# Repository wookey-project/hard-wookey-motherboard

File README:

# WooKey Mainboard PCB

## Introduction

Wookey | https://wookey-project.github.io/
Copyright 2018 The wookey project team <wookey@ssi.gouv.fr>

The Wookey from [ANSSI](https://www.ssi.gouv.fr) is an open source
hardware design, implementing an Encrypted Flash Drives.

This repository is aimed towards developers.

### Revision information

This directory contains the hardware design for the Wookey board, first public version (Wookey V2).

### PCB editing tools

All PCB files (schematic and PCB layout) have been designed using the KiCad EDA.
This Cross Platform and Open Source Electronics Design Automation Suite can be downloaded
on http://kicad-pcb.org/.

## Production files generation 101

### Configure the project

KiCad binaries location may change regarding your operating system.
This is why you have to set your environment.
This is done by sourcing the `setenv.sh` script. This script exports
all paths that are required in order to automaticaly generate the production files.

Most of the time, the paths proposed in this script are not the one you use in your specific installation.
The `setenv.sh` script support easy variables overloading by including a `setenv.local.sh` script file if this file exists in the same directory.
If you need to overload some of the variables of the `setenv.sh` script, just add them to your own `setenv.local.sh` file.
Here is an example to define KiCad environement path on Apple Mac OS.

```
  $ echo "export PYTHON_BIN_PATH = /Applications/KiCad/kicad.app/Contents/Frameworks/Python.framework/Versions/2.7/bin/python" > setenv.local.sh
  $ source setenv.sh
  Loading local SDK settings...
  =========================================================
  === Kicad environment configuration
  =========================================================
  PYTHON_BIN_PATH   = /Applications/KiCad/kicad.app/Contents/Frameworks/Python.framework/Versions/2.7/bin/python
  PYTHON_PATH     = /Applications/Kicad/kicad.app/Contents/Frameworks/python/site-packages
  BOM_GEN_PATH = /Applications/Kicad/kicad.app/Contents/SharedSupport/plugins/bom2grouped_csv.xsl
  TOOLS_PATH = ../../../tools
  =========================================================
```

The production files can be generated using the following command.

```
$ make
```

This will generate the production files in a new sub directory.
The directory name may differ according the project your are working with.

## PCB Pinout

## PCB Layers

### PCB TOP layer

### PCB BOTTOM layer

### Layers

Order and type of copper layers:
  TOP:  signal, front components
  GND:  ground plane
  PWR:  ground and power plane
  BOT:  signal, back components

### Stackup
4 layers, 1.6mm thickness
Outer layers 1 oz base copper foil
Inner layers 0.5 oz base copper foil

Electroless Nickel Immersion Gold (ENIG) surface finish

solder resist   0.0254mm
copper          0.0356mm    L1 (TOP)
FR408 prepreg   0.1702mm
copper          0.0178mm    L2 (GND)
FR408           1.1938mm
copper          0.0178mm    L3 (PWR)
FR408 prepreg   0.1702mm
copper          0.0356mm    L4 (BOT)
solder resist   0.0254mm

The substrate for both the core and prepreg is FR408,
with a dielectric constant of 3.66 at 1GHz.
The prepreg is comprised of 2 layers of Isola 2113.

## Regulatory compliance & handling

The Wookey board is intended for use as a development platform for hardware
or software. The board is an open system design, which does not include a
shielded enclosure. This may cause interference to other electrical or
electronic devices in close proximity. In a domestic environment, this product
may cause radio interference in which case the user may be required to take
adequate measures. In addition, this board should not be used near any medical
equipment or RF devices.

The board is sensitive to ESD. Hold the board only by its edges. After removing
the board from its box, place it on a grounded, static-free surface.

The board can become hot, like any fan-less design, during continuous high CPU
loads, mind its temperature while handling it.

## License

Wookey | https://wookey-project.github.io/
Copyright 2018 The wookey project team <wookey@ssi.gouv.fr>

This is an open hardware design licensed under the terms of the CERN Open
Hardware Licence (OHL) v1.2.

You may redistribute and modify this documentation under the terms of the CERN
OHL v.1.2 (http://ohwr.org/cernohl). This documentation is distributed WITHOUT
ANY EXPRESS OR IMPLIED WARRANTY, INCLUDING OF MERCHANTABILITY, SATISFACTORY
QUALITY AND FITNESS FOR A PARTICULAR PURPOSE. Please see the CERN OHL v.1.2 for
applicable conditions.

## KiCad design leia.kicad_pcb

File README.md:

# WooKey Mainboard PCB

## Introduction

Wookey | https://wookey-project.github.io/
Copyright 2018 ANSSI

Authors: The Wookey project Team <wookey@ssi.gouv.fr>

The Wookey from [ANSSI](https://www.ssi.gouv.fr) is an open source
hardware design, implementing an Encrypted Flash Drives.

This repository is aimed towards developers.

### Revision information

This directory contains the hardware design for the Wookey board, first public version (Wookey V2).

### PCB editing tools

All PCB files (schematic and PCB layout) have been designed using the KiCad EDA.
This Cross Platform and Open Source Electronics Design Automation Suite can be downloaded
on http://kicad.org/.

## Production files generation 101

### Configure the project

KiCad binaries location may change regarding your operating system.
This is why you have to set your environment.
This is done by sourcing the `setenv.sh` script. This script exports
all paths that are required in order to automaticaly generate the production files.

Most of the time, the paths proposed in this script are not the one you use in your specific installation.
The `setenv.sh` script support easy variables overloading by including a `setenv.local.sh` script file if this file exists in the same directory.
If you need to overload some of the variables of the `setenv.sh` script, just add them to your own `setenv.local.sh` file.
Here is an example to define KiCad environement path on Apple Mac OS.

```
  $ echo "export PYTHON_BIN_PATH = /Applications/KiCad/kicad.app/Contents/Frameworks/Python.framework/Versions/2.7/bin/python" > setenv.local.sh
  $ source setenv.sh
  Loading local SDK settings...
  =========================================================
  === Kicad environment configuration
  =========================================================
  PYTHON_BIN_PATH   = /Applications/KiCad/kicad.app/Contents/Frameworks/Python.framework/Versions/2.7/bin/python
  PYTHON_PATH     = /Applications/Kicad/kicad.app/Contents/Frameworks/python/site-packages
  BOM_GEN_PATH = /Applications/Kicad/kicad.app/Contents/SharedSupport/plugins/bom2grouped_csv.xsl
  TOOLS_PATH = ../../../tools
  =========================================================
```

The production files can be generated using the following command.

```
$ make
```

This will generate the production files in a new sub directory.
The directory name may differ according the project your are working with.

## PCB Pinout

## PCB Layers

### PCB TOP layer

### PCB BOTTOM layer

### Layers

Order and type of copper layers:
  TOP:  signal, front components
  GND:  ground plane
  PWR:  ground and power plane
  BOT:  signal, back components

### Stackup
4 layers, 1.6mm thickness
Outer layers 1 oz base copper foil
Inner layers 0.5 oz base copper foil

Electroless Nickel Immersion Gold (ENIG) surface finish

solder resist   0.0254mm
copper          0.0356mm    L1 (TOP)
FR408 prepreg   0.1702mm
copper          0.0178mm    L2 (GND)
FR408           1.1938mm
copper          0.0178mm    L3 (PWR)
FR408 prepreg   0.1702mm
copper          0.0356mm    L4 (BOT)
solder resist   0.0254mm

The substrate for both the core and prepreg is FR408,
with a dielectric constant of 3.66 at 1GHz.
The prepreg is comprised of 2 layers of Isola 2113.

## Regulatory compliance & handling

The Wookey board is intended for use as a development platform for hardware
or software. The board is an open system design, which does not include a
shielded enclosure. This may cause interference to other electrical or
electronic devices in close proximity. In a domestic environment, this product
may cause radio interference in which case the user may be required to take
adequate measures. In addition, this board should not be used near any medical
equipment or RF devices.

The board is sensitive to ESD. Hold the board only by its edges. After removing
the board from its box, place it on a grounded, static-free surface.

The board can become hot, like any fan-less design, during continuous high CPU
loads, mind its temperature while handling it.

## License

Wookey | https://wookey-project.github.io/

Copyright 2019 ANSSI

Authors: The Wookey project Team <wookey@ssi.gouv.fr>

This is an open hardware design licensed under the terms of the CERN Open
Hardware Licence (OHL) v1.2.

You may redistribute and modify this documentation under the terms of the CERN
OHL v.1.2 (http://ohwr.org/cernohl). This documentation is distributed WITHOUT
ANY EXPRESS OR IMPLIED WARRANTY, INCLUDING OF MERCHANTABILITY, SATISFACTORY
QUALITY AND FITNESS FOR A PARTICULAR PURPOSE. Please see the CERN OHL v.1.2 for
applicable conditions.

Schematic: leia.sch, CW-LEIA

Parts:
C1003, C4004: 0.1uF 35V Tant; CP_EIA-3216-18_Kemet-A; MFG Part Num T491A104K035AT
FID1001, FID1002, FID1003, FID1004, FID1005, FID1006: FIDUCIAL-RESCUE-rescue; Fiducial_1mm_Mask2mm
HOLE1, HOLE2: HOLE; MountingHole_2.2mm_M2_ISO14580_Pad
J6: EXT_READER_VCC; SMA_Amphenol_132289_EdgeMount; MFG Part Num 132289
J1002: READER_GND; PinHeader_2x03_P2.54mm_Vertical; MFG Part Num 90131-0763
J1003: READER_VDD; PinHeader_2x03_P2.54mm_Vertical; MFG Part Num 90131-0763
J1101: TARGET_PWR; PinHeader_2x03_P2.54mm_Vertical; MFG Part Num 90131-0763
J1102: TARGET_GND; PinHeader_2x03_P2.54mm_Vertical; MFG Part Num 90131-0763
J1103: TARGET_EXT_PWR; SMA_Amphenol_132289_EdgeMount; MFG Part Num 132289
J1112: TARGET_SHUNT; SMA_Amphenol_132289_EdgeMount; MFG Part Num 132289
JP1102: SHUNT Bypass; PinHeader_1x02_P2.54mm_Vertical; MFG Part Num 90120-0762
P523: CMD; PinHeader_2x04_P2.54mm_Vertical; MFG Part Num 826632-4
R1112: 0.1 1%; R_0603_1608Metric; MFG Part Num RL0603FR-070R1L
TP1001: VDDD; TestPoint_Keystone_5000-5004_Miniature; MFG Part Num 5003
TP1002: DGND; TestPoint_Keystone_5000-5004_Miniature; MFG Part Num 5002; Mouser Price/Stock 2301279
TP1101: VDDA; TestPoint_Pad_D1.0mm
TP1112: GNDA; TestPoint_Pad_D1.0mm
TP5001: VDDA; TestPoint_Keystone_5000-5004_Miniature; MFG Part Num 5000
TP5002: GNDA; TestPoint_Keystone_5000-5004_Miniature; MFG Part Num 5001; Mouser Price/Stock 5001
U520: FOD8012A; SOIC-8_3.9x4.9mm_P1.27mm

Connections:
/EXT_READER_GND: J6.2 (Ext), J1002.6
/EXT_READER_VCC: J6.1 (In), J1003.5
/GNDCARD: J1112.1 (In), JP1102.1, R1112.1; also elsewhere on the board
/GND_CONSOLE: C1003.2, P523.7, U520.5 (GND2)
/RX_CMD: U520.2 (VOA); also elsewhere on the board
/RX_CONSOLE: P523.3, U520.7 (VINA)
/TX_CMD: U520.3 (VINB); also elsewhere on the board
/TX_CONSOLE: P523.5, U520.6 (VOB)
/USB_READER_VCC: J1003.1; also elsewhere on the board
/VDD_CONSOLE: C1003.1, P523.1, U520.8 (VDD2)
/iface_ufo/RX: P523.6; also elsewhere on the board
/iface_ufo/TX: P523.4; also elsewhere on the board
GND: J1102.2; also elsewhere on the board
GNDA: J1102.1, J1102.3, J1102.5, J1112.2 (Ext), JP1102.2, P523.8, R1112.2, TP1112.1, TP5002.1; also elsewhere on the board
GNDD: C4004.2, J1002.1, J1002.3, J1002.5, TP1002.1, U520.4 (GND1); also elsewhere on the board
GNDPWR: J1002.2; also elsewhere on the board
unnamed: J1101.6, J1103.1 (In)
unnamed: J1102.6, J1103.2 (Ext)
VCOM: J1101.2; also elsewhere on the board
VDD: C4004.1, J1003.2, J1003.4, J1003.6, TP1001.1, U520.1 (VDD1); also elsewhere on the board
VDDA: J1101.1, J1101.3, J1101.5, P523.2, TP1101.1, TP5001.1; also elsewhere on the board

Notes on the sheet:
Since LEIA embed an SMA for the shunt resistor, we do not need to connect SHUNT signal to the CW308 board
VDDD and GNDD are connected to optocouplers reader side
User can choose between external power supply or CW power supply.
User can choose to connect the CMD Console to the CW or something else. In this case optocoupler power supply should be provided by the device connected to the CMD Console.
JMP 1101 VDDA 1-2 CW-POWER 5-6 EXT-POWER
JMP 1102 GNDA 1-2 CW-GND 5-6 EXT-GND

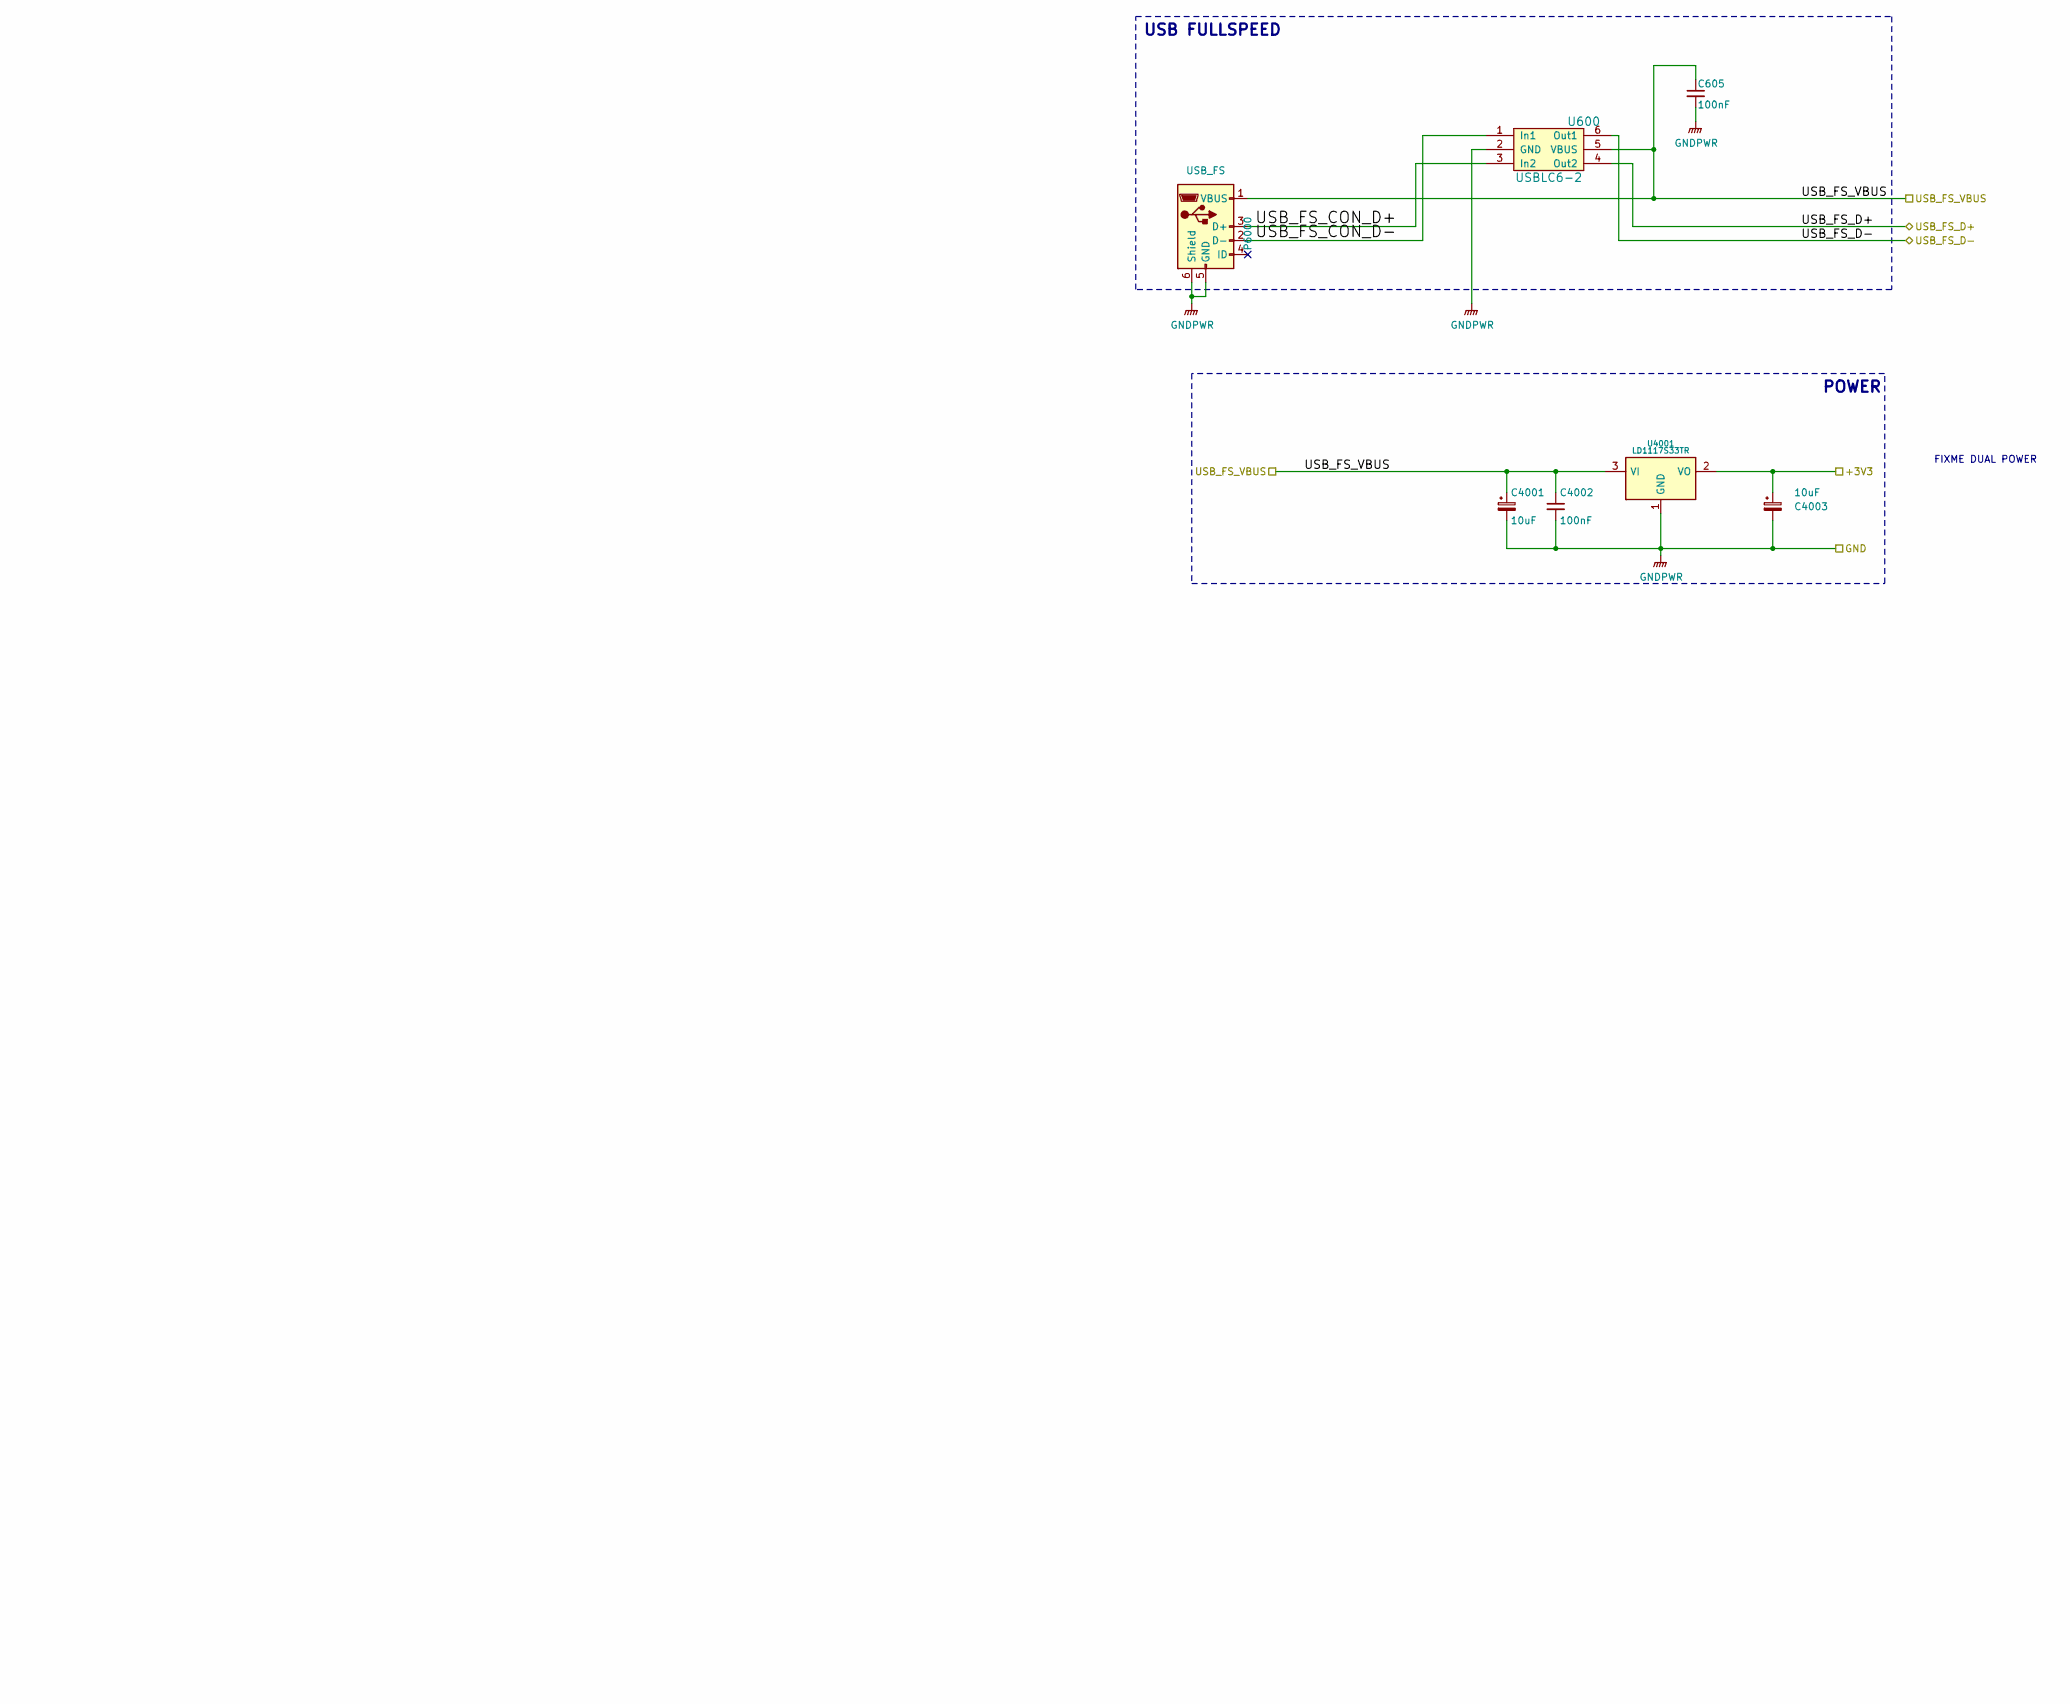
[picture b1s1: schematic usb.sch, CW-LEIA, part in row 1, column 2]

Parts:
C605, C4002: 100nF; C_0603_1608Metric; MFG Part Num GRM188R71H104KA93D
C4001, C4003: 10uF; CP_EIA-3216-18_Kemet-A; MFG Part Num TP8M106M6R3C
P6000: USB_FS; USB_Micro-B-MOLEX_105017-0001; MFG Part Num 105017-0001
U600: USBLC6-2; SOT-23-6; MFG Part Num USBLC6-2SC6
U4001: LD1117S33TR; SOT-223; MFG Part Num LD1117S33TR

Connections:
/USB_READER_VCC: C4003.1, U4001.2 (VO); also elsewhere on the board
/cpu/USB_FS_D+: U600.4 (Out2); also elsewhere on the board
/cpu/USB_FS_D-: U600.6 (Out1); also elsewhere on the board
/cpu/USB_FS_VBUS: C605.1, C4001.1, C4002.1, P6000.1 (VBUS), U600.5 (VBUS), U4001.3 (VI); also elsewhere on the board
/usb/USB_FS_CON_D+: P6000.3 (D+), U600.3 (In2)
/usb/USB_FS_CON_D-: P6000.2 (D-), U600.1 (In1)
GNDPWR: C605.2, C4001.2, C4002.2, C4003.2, P6000.5 (GND), P6000.6 (Shield), U600.2 (GND), U4001.1 (GND); also elsewhere on the board

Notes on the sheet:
USB FULLSPEED
POWER
FIXME DUAL POWER

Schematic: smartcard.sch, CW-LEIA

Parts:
C1001: 10uF; C_0603_1608Metric; MFG Part Num TP8M106M6R3C
C1002: 100nF; C_0603_1608Metric; MFG Part Num GRM188R71H104KA93D
C1101, C1108, C1201, C1208, C1301, C1308, C1401, C1408, C1501, C1508, C1601, C1608, C1701, C1708, C1801, C1806, C1902, C5001, C5002, C5003: 0.1uF 35V Tant; CP_EIA-3216-18_Kemet-A; MFG Part Num T491A104K035AT
D3001: VDDA; LED_0603_1608Metric_Castellated; MFG Part Num TLMS1100-GS08..
J1001: FILTER; PinHeader_2x03_P2.54mm_Vertical; MFG Part Num 90131-0763
J1706: TARGET_TRIG; SMA_Amphenol_132289_EdgeMount; MFG Part Num 132289
JP1500: TEARING; PinHeader_1x02_P2.54mm_Vertical; MFG Part Num 90120-0762
P1000: ISO7816_NO; VJW53666; MFG Part Num 7312P0225A13LF
Q5001, Q5002: BSS84; SOT-23; MFG Part Num BSS84
R1001: 20k; R_0603_1608Metric; MFG Part Num RCA060320K0FKEA
R1007, R1422, R1902: 22k; R_0603_1608Metric; MFG Part Num RCA060320K0FKEA
R1306, R1506: 10k; R_0603_1608Metric; MFG Part Num CRCW060310K0JNEA
R3001: 470; R_0603_1608Metric; MFG Part Num CRCW0603470RFKEA
R5002, R5003: DNP; R_0603_1608Metric; MFG Part Num RCA060347K0FKEA
U1100, U1200, U1300, U1400, U1500, U1600, U1700, U1800, U5001: FOD8001; SOIC-8_3.9x4.9mm_P1.27mm; MFG Part Num FOD8001
U1900, U5002: ADG719-EP; TSOT-23-6; MFG Part Num ADG719BRTZ-REEL7

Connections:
/GNDCARD: P1000.C5 (GND); also elsewhere on the board
/cpu/CARD_CLK: U1200.2 (Vin); also elsewhere on the board
/cpu/CARD_CT: U1600.6 (Vout); also elsewhere on the board
/cpu/CARD_IO: U1900.5 (D); also elsewhere on the board
/cpu/CARD_PWR_EN: U1500.2 (Vin); also elsewhere on the board
/cpu/CARD_RESET: U1100.2 (Vin); also elsewhere on the board
/cpu/CARD_VPP: U1300.2 (Vin); also elsewhere on the board
/cpu/CARD_~R~W: U1900.1 (IN), U5001.2 (Vin); also elsewhere on the board
/cpu/TRIGGER: U1700.2 (Vin); also elsewhere on the board
/dfu smartcard/CRD_CLK: P1000.C3 (CLK), U1200.6 (Vout)
/dfu smartcard/CRD_CT: P1000.SW1, R1001.2, U1600.2 (Vin)
/dfu smartcard/CRD_IO: P1000.C7 (I/O), R1007.2, U5002.5 (D)
/dfu smartcard/CRD_PWR: J1001.1, P1000.C1 (VCC), Q5002.3 (D), R1506.1
/dfu smartcard/CRD_RST: P1000.C2 (RST), U1100.6 (Vout)
/dfu smartcard/CRD_VPP: P1000.C6 (VPP), Q5001.3 (D), R1306.1
/dfu smartcard/IO_IN: R1422.2, U1400.2 (Vin), U1900.6 (S2)
/dfu smartcard/IO_OUT: R1902.2, U1800.6 (Vout), U1900.4 (S1)
/dfu smartcard/TRIGGER_OUT: J1706.1 (In), U1700.6 (Vout)
GNDA: C1001.2, C1002.2, C1108.2, C1208.2, C1308.2, C1408.2, C1508.2, C1608.2, C1708.2, C1801.2, C5002.2, C5003.2, D3001.1 (K), J1001.5, J1706.2 (Ext), P1000.SW2, R1306.2, R1506.2, U1100.5 (GND2), U1200.5 (GND2), U1300.5 (GND2), U1400.5 (GND2), U1500.5 (GND2), U1600.4 (GND1), U1700.5 (GND2), U1800.4 (GND1), U5001.5 (GND2), U5002.3 (GND); also elsewhere on the board
GNDD: C1101.2, C1201.2, C1301.2, C1401.2, C1501.2, C1601.2, C1701.2, C1806.2, C1902.2, C5001.2, U1100.4 (GND1), U1200.4 (GND1), U1300.4 (GND1), U1400.4 (GND1), U1500.4 (GND1), U1600.5 (GND2), U1700.4 (GND1), U1800.5 (GND2), U1900.3 (GND), U5001.4 (GND1); also elsewhere on the board
unnamed: C1001.1, C1002.1, J1001.2, J1001.4, J1001.6
unnamed: D3001.2 (A), R3001.2
unnamed: JP1500.1, U1500.6 (Vout)
unnamed: JP1500.2, Q5002.1 (G)
unnamed: Q5001.1 (G), U1300.6 (Vout)
unnamed: R5002.2, U1400.6 (Vout), U5002.6 (S2)
unnamed: R5003.2, U1800.2 (Vin), U5002.4 (S1)
unnamed: U5001.6 (Vout), U5002.1 (IN)
VDD: C1101.1, C1201.1, C1301.1, C1401.1, C1501.1, C1601.1, C1701.1, C1806.1, C1902.1, C5001.1, R1422.1, R1902.1, U1100.1 (VDD1), U1200.1 (VDD1), U1300.1 (VDD1), U1400.1 (VDD1), U1500.1 (VDD1), U1600.8 (VDD2), U1700.1 (VDD1), U1800.8 (VDD2), U1900.2 (VDD), U5001.1 (VDD1); also elsewhere on the board
VDDA: C1108.1, C1208.1, C1308.1, C1408.1, C1508.1, C1608.1, C1708.1, C1801.1, C5002.1, C5003.1, Q5001.2 (S), Q5002.2 (S), R1001.1, R1007.1, R3001.1, R5002.1, R5003.1, U1100.8 (VDD2), U1200.8 (VDD2), U1300.8 (VDD2), U1400.8 (VDD2), U1500.8 (VDD2), U1600.1 (VDD1), U1700.8 (VDD2), U1800.1 (VDD1), U5001.8 (VDD2), U5002.2 (VDD); also elsewhere on the board

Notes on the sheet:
TruthTable VI Vled VO H OFF H L ON L

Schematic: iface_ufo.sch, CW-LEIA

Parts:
J6000: CW308_TARGETCON; CW308T_CONNBOARD
J6200: CW_PWR; PinHeader_2x06_P2.54mm_Vertical; MFG Part Num 90131-0766

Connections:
/iface_ufo/CW308_1.2: J6000.C11 (VCC1.2), J6200.9
/iface_ufo/CW308_1.8: J6000.C12 (VCC1.8), J6200.7
/iface_ufo/CW308_2.5: J6000.C13 (VCC2.5), J6200.5
/iface_ufo/CW308_3.3: J6000.C14 (VCC3.3), J6200.3
/iface_ufo/CW308_5.0: J6000.C15 (VCC5.0), J6200.1
/iface_ufo/RX: J6000.A8 (GPIO2/RX); also elsewhere on the board
/iface_ufo/TX: J6000.A7 (GPIO1/TX); also elsewhere on the board
GND: J6000.C17 (GND); also elsewhere on the board
VCOM: J6000.C8 (FILTIN), J6200.2, J6200.4, J6200.6, J6200.8, J6200.10, J6200.12; also elsewhere on the board
VDDA: J6000.A20 (VREF); also elsewhere on the board

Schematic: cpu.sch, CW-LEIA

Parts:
C500, C506, C511, C514, C519, C521, C522, C528, C550, C575: 100nF; C_0603_1608Metric; MFG Part Num GRM188R71H104KA93D
C549, C573: 2.2uF; C_0603_1608Metric; MFG Part Num GRM188R61C225KE15D
D110: LED BLUE; LED_0603_1608Metric_Castellated; MFG Part Num VLMB1300-GS08
D111: LED GREEN; LED_0603_1608Metric_Castellated; MFG Part Num VLMTG1300-GS08
D112: VDD; LED_0603_1608Metric_Castellated; MFG Part Num TLMS1100-GS08..
JP100: BOOT1; PinHeader_1x02_P2.54mm_Vertical; MFG Part Num 90120-0762
JP101: BOOT0; PinHeader_1x02_P2.54mm_Vertical; MFG Part Num 90120-0762
P542: TP4; TestPoint_Pad_D1.0mm
P543: TP5; TestPoint_Pad_D1.0mm
P545: TP7; TestPoint_Pad_D1.0mm
P546: TP8; TestPoint_Pad_D1.0mm
P547: TP9; TestPoint_Pad_D1.0mm
P548: TP10; TestPoint_Pad_D1.0mm
P592: UART1; PinHeader_1x03_P2.54mm_Vertical; MFG Part Num 90120-0763
P593: SWD; PinHeader_1x05_P2.54mm_Vertical; MFG Part Num 90120-0765
R100, R503, R514: 10K; R_0603_1608Metric; MFG Part Num CRCW060310K0FKEAHP
R104, R110, R111, R112: 470; R_0603_1608Metric; MFG Part Num CRCW0603470RFKEA
SW503: DFU; KSR_TACTILE_SWITCH; MFG Part Num KSR231G LFS
SW514: RESET; KSR_TACTILE_SWITCH; MFG Part Num KSR231G LFS
U500: STM32F439VIT6; TQFP-100_14x14mm_P0.5mm; MFG Part Num STM32F439VIT6

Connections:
/RX_CMD: U500.24 (PA1); also elsewhere on the board
/TX_CMD: U500.23 (PA0); also elsewhere on the board
/cpu/BOOT0: JP101.1, U500.94 (BOOT0)
/cpu/BOOT1: JP100.2, U500.37 (PB2)
/cpu/CARD_CLK: U500.29 (PA4), U500.90 (PB4); also elsewhere on the board
/cpu/CARD_CT: U500.79 (PC11); also elsewhere on the board
/cpu/CARD_IO: U500.25 (PA2); also elsewhere on the board
/cpu/CARD_PWR_EN: U500.88 (PD7); also elsewhere on the board
/cpu/CARD_RESET: U500.80 (PC12); also elsewhere on the board
/cpu/CARD_VPP: U500.78 (PC10); also elsewhere on the board
/cpu/CARD_~R~W: U500.2 (PE3); also elsewhere on the board
/cpu/DFU: R503.1, SW503.2, U500.30 (PA5)
/cpu/LED0_PC4: R111.1, U500.33 (PC4)
/cpu/LED1_PC5: R110.1, U500.34 (PC5)
/cpu/NRST: C514.1, P593.5, R514.2, SW514.1, U500.14 (NRST)
/cpu/TCK: P593.2, U500.76 (PA14)
/cpu/TMS: P593.4, U500.72 (PA13)
/cpu/TRIGGER: U500.77 (PA15); also elsewhere on the board
/cpu/UART1_RX_PB7: P592.2, U500.93 (PB7)
/cpu/UART1_TX_PB6: P592.1, U500.92 (PB6)
/cpu/USB_FS_D+: U500.71 (PA12); also elsewhere on the board
/cpu/USB_FS_D-: U500.70 (PA11); also elsewhere on the board
/cpu/USB_FS_VBUS: U500.68 (PA9); also elsewhere on the board
GNDD: C500.2, C506.2, C511.2, C514.2, C519.2, C521.2, C522.2, C528.2, C549.2, C550.2, C573.2, C575.2, D110.1 (K), D111.1 (K), D112.1 (K), P592.3, P593.3, R104.2, R503.2, SW514.2, U500.10 (VSS), U500.20 (VSSA), U500.27 (VSS), U500.74 (VSS), U500.99 (VSS); also elsewhere on the board
unnamed: C549.1, U500.49 (VCAP_1)
unnamed: C573.1, U500.73 (VCAP_2)
unnamed: D110.2 (A), R110.2
unnamed: D111.2 (A), R111.2
unnamed: D112.2 (A), R112.2
unnamed: JP100.1, R100.2
unnamed: JP101.2, R104.1
unnamed: P542.1, U500.42 (PE11)
unnamed: P543.1, U500.43 (PE12)
unnamed: P545.1, U500.45 (PE14)
unnamed: P546.1, U500.46 (PE15)
unnamed: P547.1, U500.81 (PD0)
unnamed: P548.1, U500.82 (PD1)
VDD: C500.1, C506.1, C511.1, C519.1, C521.1, C522.1, C528.1, C550.1, C575.1, P593.1, R100.1, R112.1, R514.1, SW503.1, U500.6 (VBAT), U500.11 (VDD), U500.19 (VDD), U500.21 (VREF+), U500.22 (VDDA), U500.28 (VDD), U500.50 (VDD), U500.75 (VDD), U500.100 (VDD); also elsewhere on the board

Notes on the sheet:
BOOT MODE
LED
EXTENSION & DEBUG
Boot0 = 0 => Flash memory aliased at 0x0000000
Since the READER and the Target have separated power domains, the reader JTAG and the Debug UART are not connected to the CW308 board.

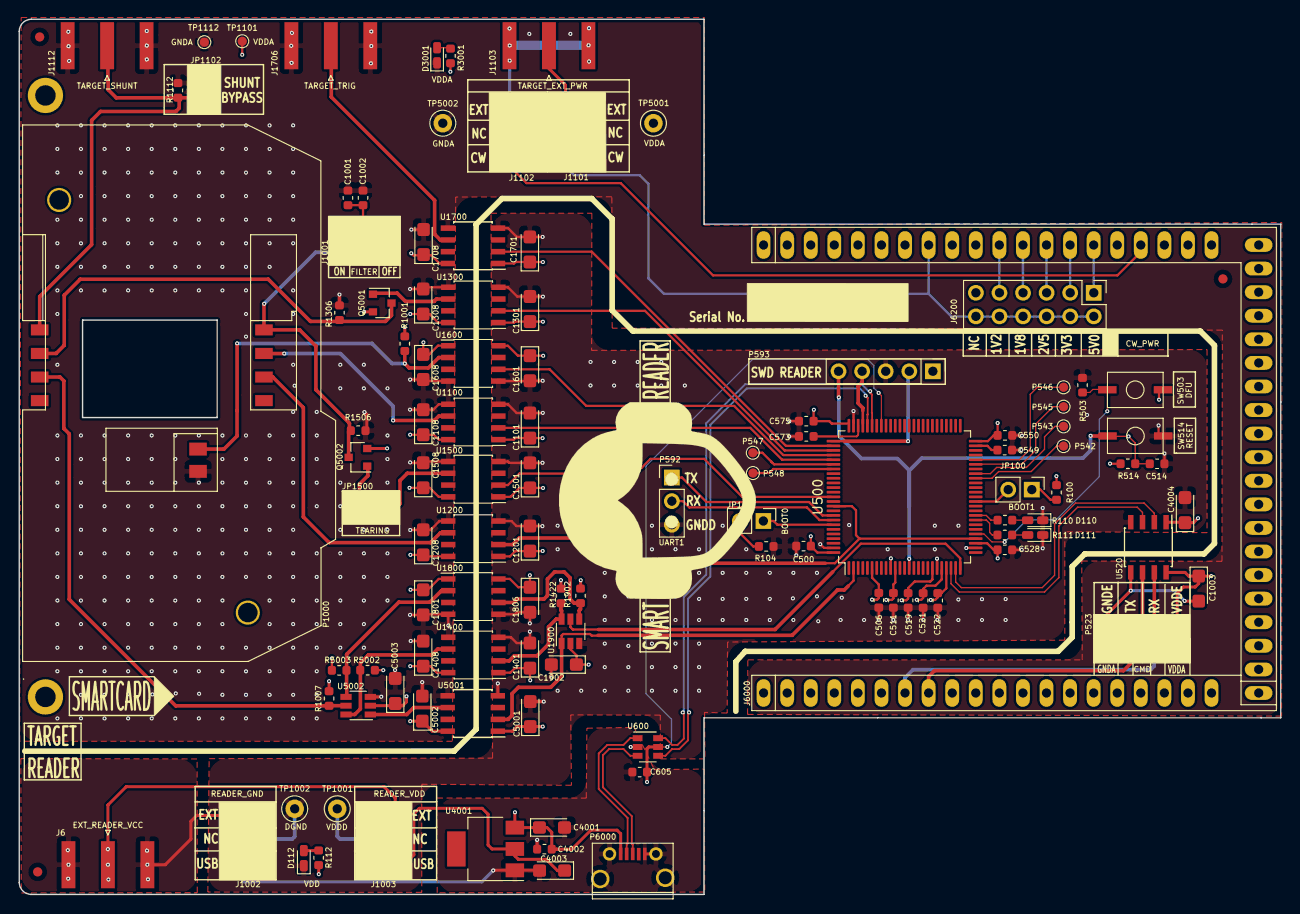
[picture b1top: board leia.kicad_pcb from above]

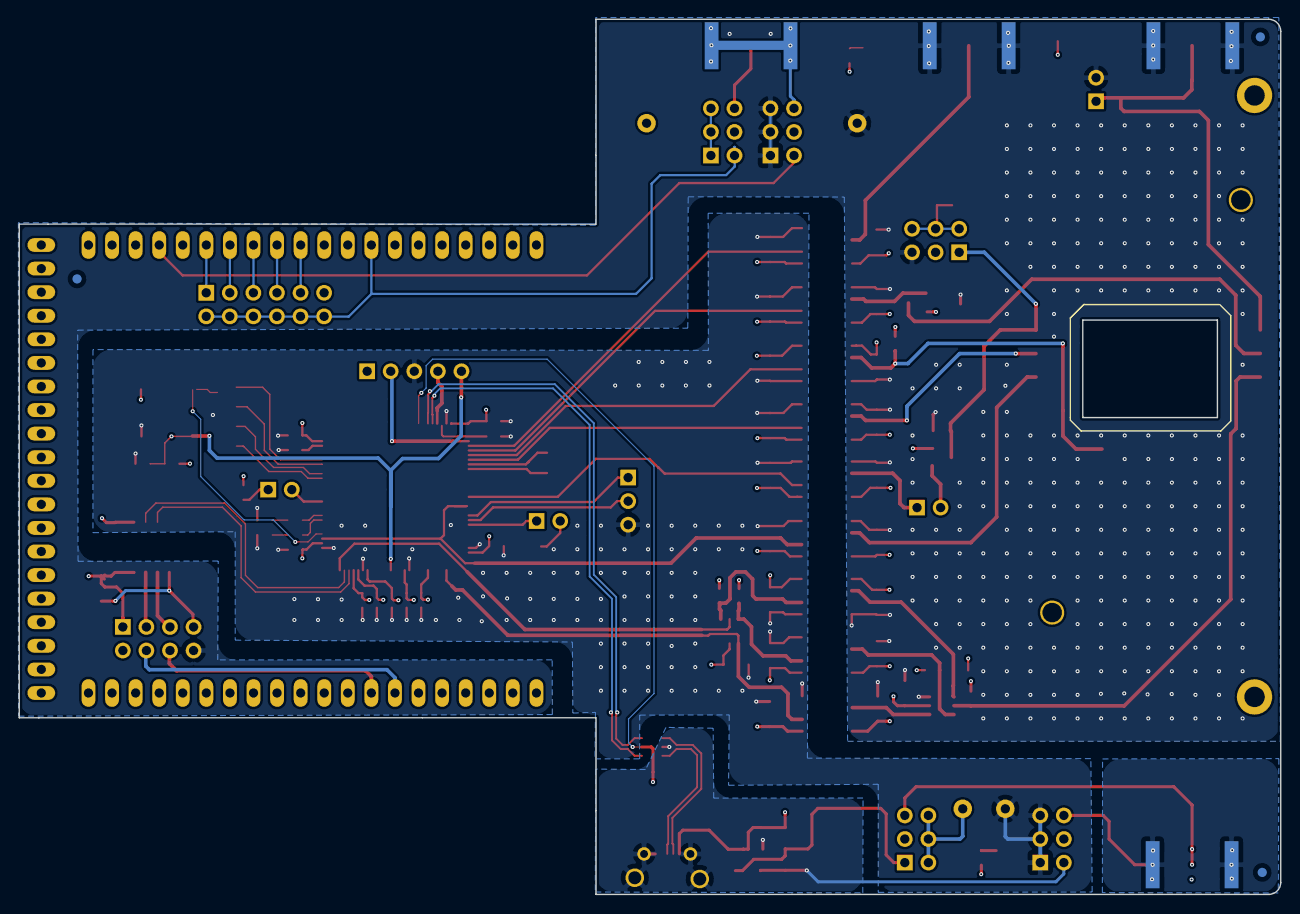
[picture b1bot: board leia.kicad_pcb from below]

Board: 4 copper layers, 135.9 x 94.3 mm, 120 parts (3 on the bottom side), 79 nets.

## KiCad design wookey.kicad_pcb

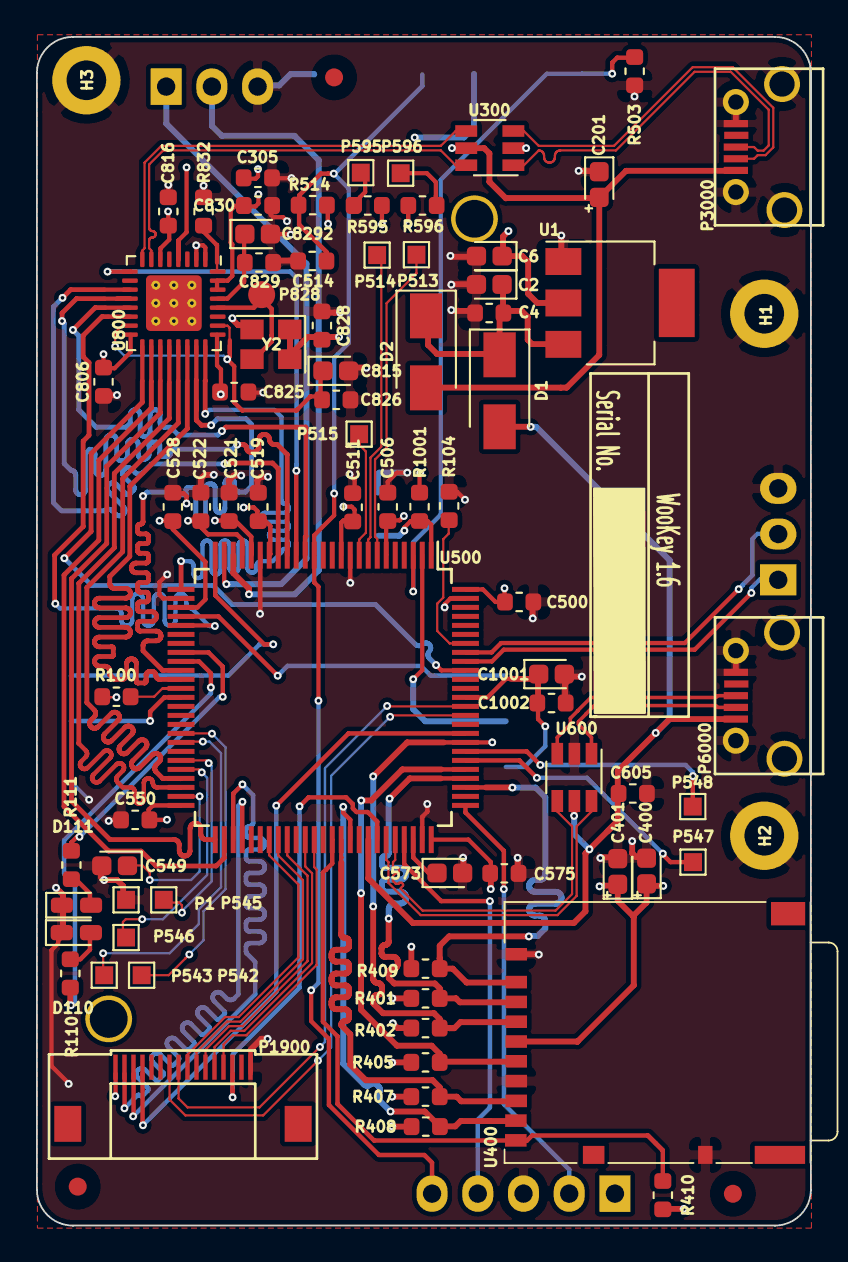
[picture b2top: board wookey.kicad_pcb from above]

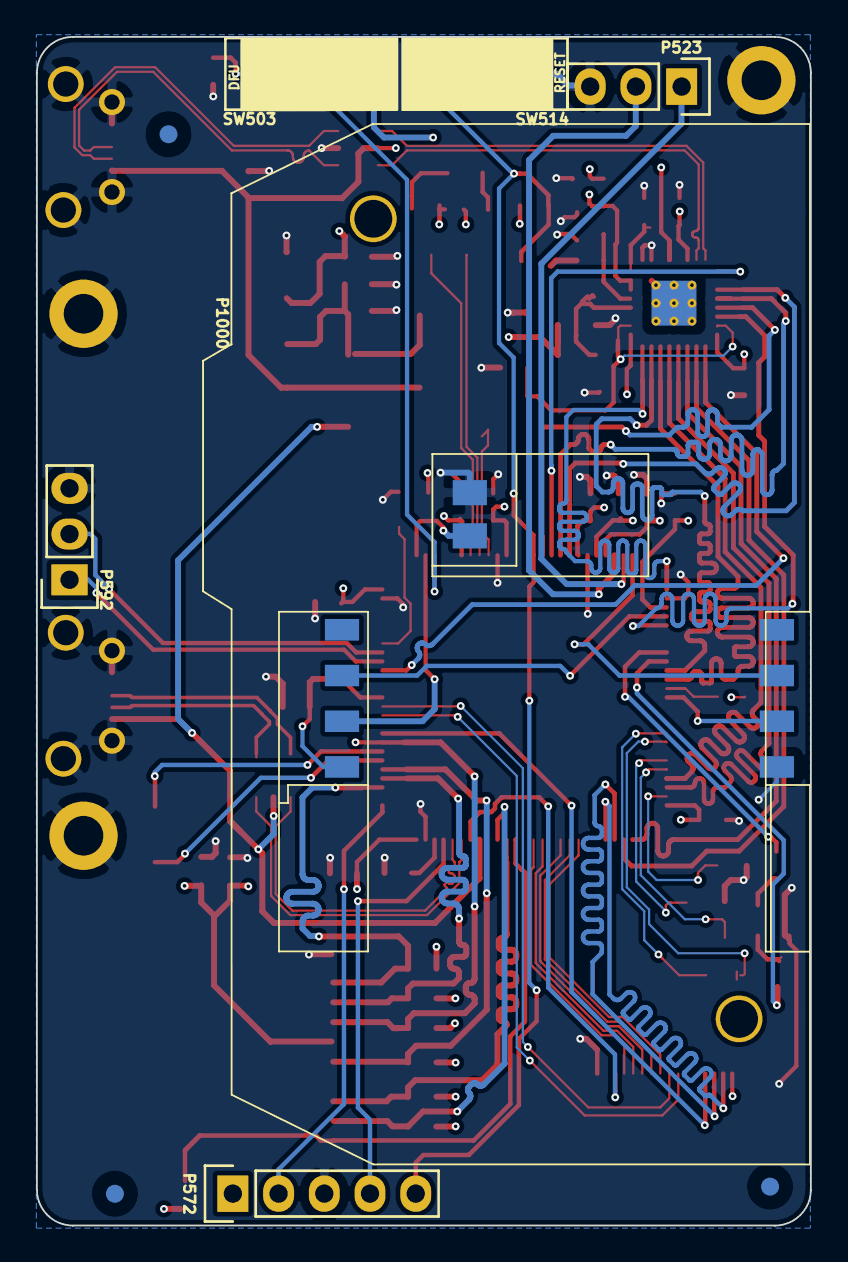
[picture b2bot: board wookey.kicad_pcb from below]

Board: 4 copper layers, 43.0 x 66.0 mm, 90 parts (6 on the bottom side), 81 nets.

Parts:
C2, C6, C1001: 10uF; CP_EIA-1608-08_AVX-J
C4, C305, C500, C506, C511, C514, C519, C521, C522, C528, C550, C575, C605, C806, C816, C825, C826, C829, C830, C1002: 100nF; C_0603_1608Metric
C201, C815, C8292: 4.7uF; CP_EIA-1608-08_AVX-J
C400: 10uF 10V; CP_EIA-1608-08_AVX-J
C401: 0.1uF 6,3V; CP_EIA-1608-08_AVX-J
C549, C573: 2.2uF; CP_EIA-1608-08_AVX-J
C828: 0.01uF; C_0603_1608Metric
D1, D2: STPS1L30A; D_SMA
D110: LED BLUE; LED_0603_1608Metric_Castellated
D111: LED GREEN; LED_0603_1608Metric_Castellated
FID1, FID2, FID3: FIDUCIAL; Fiducial_1mm_Dia_2.54mm_Outer_CopperTop
FID4, FID5, FID6: FIDUCIAL; Fiducial_1mm_Dia_2.54mm_Outer_CopperBottom
H1: H1; MountingHole_2.2mm_M2_ISO14580_Pad
H2: H2; MountingHole_2.2mm_M2_ISO14580_Pad
H3: H3; MountingHole_2.2mm_M2_ISO14580_Pad
P1: GND; TestPoint_Pad_1.0x1.0mm
P513: TP1; TestPoint_Pad_1.0x1.0mm
P514: TP2; TestPoint_Pad_1.0x1.0mm
P515: TP3; TestPoint_Pad_1.0x1.0mm
P523: UART4; Pin_Header_Straight_1x03
P542: TP4; TestPoint_Pad_1.0x1.0mm
P543: TP5; TestPoint_Pad_1.0x1.0mm
P545: TP7; TestPoint_Pad_1.0x1.0mm
P546: TP8; TestPoint_Pad_1.0x1.0mm
P547: TP9; TestPoint_Pad_1.0x1.0mm
P548: TP10; TestPoint_Pad_1.0x1.0mm
P572: DEBUG/PROG; Pin_Header_Straight_1x05
P592: UART1; Pin_Header_Straight_1x03
P595: I2C1_SCL; TestPoint_Pad_1.0x1.0mm
P596: I2C1_SDA; TestPoint_Pad_1.0x1.0mm
P828: XI; Measurement_Point_Round-SMD-Pad_Small
P1000: ISO7816_NO; VJW53666
P1900: CONN_FPC16; FPC16_MOLEX_52892_1633
P3000, P6000: USB_FS_OTG; USB_Micro-B-MOLEX_105017-0001
R100, R503, R514, R1001: 10K; R_0603_1608Metric
R104, R110, R111: 470; R_0603_1608Metric
R401, R402, R405, R407, R408, R409, R410, R595, R596: 47K; R_0603_1608Metric
R832: 12K [1%]; R_0603_1608Metric
SW503: DFU; KSR_TACTILE_SWITCH
SW514: RESET; KSR_TACTILE_SWITCH
U1: LD1117S33TR; SOT-223
U300, U600: USBLC6-2; TSOT-23-6
U400: MICROSDCARD; SDCARD_DM3AT
U500: STM32F439VIT6; LQFP-100_14x14mm_Pitch0.5mm
U800: USB3300; QFN-32-1EP_5x5mm_P0.5mm_EP3.1x3.1mm_ThermalVias
Y2: ASEMB-24.000MHZ-LY-T; Oscillator_SMD_Abracon_ASE-4Pin_3.2x2.5mm

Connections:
+3V3: C6.1, C400.1, C401.1, C500.1, C506.1, C511.1, C519.1, C521.1, C522.1, C528.1, C550.1, C575.1, C806.1, C816.1, C825.1, C828.1, C830.1, P572.1, P1900.1, R100.1, R401.1, R402.1, R405.1, R407.1, R408.1, R409.1, R410.1, R514.1, R595.1, R596.1, R1001.1, SW503.1, U1.2, U400.4, U500.6, U500.11, U500.19, U500.21, U500.22, U500.28, U500.50, U500.75, U500.100, U800.6, U800.16, U800.25, U800.30, U800.31, Y2.1, Y2.4
+5V: C2.1, C4.1, D1.1, D2.1, U1.3
/cpu/BOOT0: R104.1, U500.94
/cpu/BOOT1: R100.2, U500.37
/cpu/CARD_CLK: P1000.C3, U500.29
/cpu/CARD_CT: P1000.SW1, R1001.2, U500.1
/cpu/CARD_IO: P1000.C7, U500.25
/cpu/CARD_POWER: C1001.1, C1002.1, P1000.C1, U500.88
/cpu/CARD_RESET: P1000.C2, U500.2
/cpu/CARD_VPP: P1000.C6, U500.38
/cpu/DFU: R503.1, SW503.2, U500.3
/cpu/I2C1_SCL_PB8: P595.1, R595.2
/cpu/I2C1_SDA_PB9: P596.1, R596.2
/cpu/NRST: C514.1, P572.5, R514.2, SW514.1, U500.14
/cpu/SCREEN_~D~C: P1900.12, U500.61
/cpu/SD_CLK: R405.2, U400.5, U500.80
/cpu/SD_CMD: R402.2, U400.2, U500.83
/cpu/SD_D0: R407.2, U400.7, U500.65
/cpu/SD_D1: R408.2, U400.8, U500.66
/cpu/SD_D2: R409.2, U400.9, U500.78
/cpu/SD_D3: R401.2, U400.1, U500.79
/cpu/SD_D7: R410.2, U400.10, U500.64
/cpu/SPI_MISO: P1900.3, U500.53
/cpu/SPI_MOSI: P1900.2, U500.54
/cpu/SPI_SCK: P1900.4, U500.84
/cpu/TCK/SWCLK: P572.2, U500.76
/cpu/TMS/SWIO: P572.4, U500.72
/cpu/TOUCH_BUSY: P1900.10, U500.58
/cpu/TOUCH_IRQ: P1900.11, U500.59
/cpu/TP1: P513.1, U500.7
/cpu/TP2: P514.1, U500.8
/cpu/TP3: P515.1, U500.9
/cpu/UART1_RX_PB7: P592.2, U500.93
/cpu/UART1_TX_PB6: P592.1, U500.92
/cpu/UART4_RX_PA1: P523.1, U500.24
/cpu/UART4_TX_PA0: P523.2, U500.23
/cpu/USB_FS_D+: U500.71, U600.4
/cpu/USB_FS_D-: U500.70, U600.6
/cpu/USB_FS_VBUS: C605.1, D1.2, P6000.1, U500.68, U600.5
/cpu/USB_HS_HARD_RESET: U500.16, U800.9
/cpu/USB_HS_ULPI_CLK: U500.30, U800.14
/cpu/USB_HS_ULPI_D0: U500.26, U800.24
/cpu/USB_HS_ULPI_D1: U500.35, U800.23
/cpu/USB_HS_ULPI_D2: U500.36, U800.22
/cpu/USB_HS_ULPI_D3: U500.47, U800.21
/cpu/USB_HS_ULPI_D4: U500.48, U800.20
/cpu/USB_HS_ULPI_D5: U500.51, U800.19
/cpu/USB_HS_ULPI_D6: U500.52, U800.18
/cpu/USB_HS_ULPI_D7: U500.91, U800.17
/cpu/USB_HS_ULPI_DIR: U500.17, U800.12
/cpu/USB_HS_ULPI_NXT: U500.18, U800.11
/cpu/USB_HS_ULPI_STP: U500.15, U800.13
/cpu/USB_HS_VBUS: C201.2, C305.1, D2.2, P3000.1, U300.5, U800.4
/cpu/~SPI_FLASH_CS: P1900.7, U500.86
/cpu/~SPI_FONT_CS: P1900.8, U500.87
/cpu/~SPI_SCREEN_CS: P1900.14, U500.69
/cpu/~SPI_TOUCH_CS: P1900.9, U500.57
/screen/SCREEN_RESET: P1900.13, U500.62
/usb/USB_FS_CON_D+: P6000.3, U600.3
/usb/USB_FS_CON_D-: P6000.2, U600.1
/usb/USB_HS_CON_D+: P3000.3, U300.1
/usb/USB_HS_CON_D-: P3000.2, U300.3
/usb/USB_HS_D+: U300.6, U800.7
/usb/USB_HS_D-: U300.4, U800.8
GND: C2.2, C4.2, C6.2, C201.1, C305.2, C400.2, C401.2, C500.2, C506.2, C511.2, C514.2, C519.2, C521.2, C522.2, C528.2, C549.2, C550.2, C573.2, C575.2, C605.2, C806.2, C815.2, C816.2, C825.2, C826.2, C828.2, C829.2, C830.2, C1001.2, C1002.2, C8292.2, D110.1, D111.1, H1.1, H2.1, H3.1, P1.1, P523.3, P572.3, P592.3, P1000.C5, P1000.SW2, P1900.16, P3000.5, P3000.6, P6000.5, P6000.6, R104.2, R503.2, R832.2, SW514.2, U1.1, U300.2, U400.3, U400.6, U400.11, U500.10, U500.20, U500.27, U500.74, U500.99, U600.2, U800.1, U800.2, U800.33, Y2.2
LED0: R111.1, U500.33
LED1: R110.1, U500.34
unnamed: C549.1, U500.49
unnamed: C573.1, U500.73
unnamed: C815.1, C826.1, U800.15, U800.26
unnamed: C829.1, C8292.1, U800.29
unnamed: D110.2, R110.2
unnamed: D111.2, R111.2
unnamed: P542.1, U500.42
unnamed: P543.1, U500.43
unnamed: P545.1, U500.45
unnamed: P546.1, U500.46
unnamed: P547.1, U500.81
unnamed: P548.1, U500.82
unnamed: P828.1, U800.28, Y2.3
unnamed: R832.1, U800.32

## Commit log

2019-05-15 First import
2019-05-16 [enhancement] add pcb screenshots
2019-05-16 [enhancement] Add LICENSE.txt
2019-05-16 [enhancement] Reference LICENSE in files
2019-05-16 [enhancement] General cleanup
2019-05-16 [enhancement] Update README and imgs
2019-05-17 [enhancement] Add setenv.local examples
2019-05-17 [fix] Rename files.
2019-06-05 [cleanup] updating project files for LEIA
2019-06-05 [enhancement] Adding rshunt
2019-06-05 [enhancement] add new file for chipwhisperer interface:iface_ufo.sch
2019-06-05 [enhancement] add imgs
2019-06-05 [enhancement] update README
2019-06-05 [enhancement] Add BOM and Netlist files
2019-06-05 [enhancement] Add leia-rescue.lib
2019-06-05 [fix] libs
2019-08-26 [bugfix] updated copyright notice
2019-08-26 [bugfix] copyright typo
2020-06-05 [Fix] Readme
2021-11-09 Update README.md
    https://forum.kicad.info/t/warning-avoid-all-links-to-kicad-pcb-org-use-kicad-org/31521

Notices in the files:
cpu.sch:
LICENCE: CERN Open Hardware Licence v1.2
